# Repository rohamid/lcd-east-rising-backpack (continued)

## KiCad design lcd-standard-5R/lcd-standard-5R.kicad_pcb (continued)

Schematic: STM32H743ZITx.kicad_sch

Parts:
BT1: S8411-45R; CR1220-Batt-conn-S8411-45R; JLCPCB Part # C70381
C6, C7, C9, C11, C13, C14, C15, C16, C17, C18, C19, C20, C21, C22, C23, C29: 100n; C_0402_1005Metric; JLCPCB Part # C307331
C8: 1u; C_0603_1608Metric; JLCPCB Part # C15849
C10, C12: 2u2; C_0603_1608Metric; JLCPCB Part # C23630
C24: 4u7; C_0603_1608Metric; JLCPCB Part # C19666
C25, C26: 16p; C_0402_1005Metric; JLCPCB Part # C77590
C27, C28: 10p; C_0402_1005Metric; JLCPCB Part # C32949
D3: BAT54CW; SOT-23; JLCPCB Part # C37704
D4: B5819WS; D_SOD-123; JLCPCB Part # C8598
J2: SWD; PinHeader_2x07_P1.27mm_Vertical_SMD; JLCPCB Part # C5160763
J11: TAG_CONNECT; Tag-Connect_TC2050-IDC-NL_2x05_P1.27mm_Vertical
R6, R7, R8: 10K; R_0402_1005Metric; JLCPCB Part # C25744
SW1, SW2: SW_Push; SW_SPST_PTS810; JLCPCB Part # C127488
U3: STM32H743ZITx; LQFP-144_20x20mm_P0.5mm; JLCPCB Part # C114408
Y1: 25MHz; Crystal_SMD_2520-4Pin_2.5x2.0mm; JLCPCB Part # C255954
Y2: 32.768KHz; Crystal_SMD_2012-2Pin_2.0x1.2mm; JLCPCB Part # C99009

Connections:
+3V3: C6.1, C7.1, C8.1, C9.1, C11.1, C14.1, C15.1, C16.1, C17.1, C18.1, C19.1, C20.1, C21.1, C22.1, C23.1, C24.1, D3.2, J2.3, J11.7, R6.1, R7.1, SW1.2, U3.17 (VDD), U3.30 (VDD), U3.32 (VREF+), U3.33 (VDDA), U3.39 (VDD), U3.52 (VDD), U3.62 (VDD), U3.72 (VDD), U3.84 (VDD), U3.95 (VDD33_USB), U3.108 (VDD), U3.121 (VDD), U3.131 (VDD), U3.144 (VDD); also elsewhere on the board
/DISPLAY/CTP_INT: U3.80 (PD11); also elsewhere on the board
/DISPLAY/CTP_RST: U3.98 (PC8); also elsewhere on the board
/DISPLAY/CTP_SCL: U3.100 (PA8); also elsewhere on the board
/DISPLAY/CTP_SDA: U3.99 (PC9); also elsewhere on the board
/DISPLAY/CTP_WAKE: U3.88 (PG3); also elsewhere on the board
/DISPLAY/LCD_B0: U3.3 (PE4); also elsewhere on the board
/DISPLAY/LCD_B1: U3.127 (PG12); also elsewhere on the board
/DISPLAY/LCD_B2: U3.122 (PD6); also elsewhere on the board
/DISPLAY/LCD_B3: U3.126 (PG11); also elsewhere on the board
/DISPLAY/LCD_B4: U3.102 (PA10); also elsewhere on the board
/DISPLAY/LCD_B5: U3.37 (PA3); also elsewhere on the board
/DISPLAY/LCD_B6: U3.139 (PB8); also elsewhere on the board
/DISPLAY/LCD_B7: U3.140 (PB9); also elsewhere on the board
/DISPLAY/LCD_BLK: U3.110 (PA15); also elsewhere on the board
/DISPLAY/LCD_CLK: U3.92 (PG7); also elsewhere on the board
/DISPLAY/LCD_DE: U3.22 (PF10); also elsewhere on the board
/DISPLAY/LCD_G0: U3.4 (PE5); also elsewhere on the board
/DISPLAY/LCD_G1: U3.5 (PE6); also elsewhere on the board
/DISPLAY/LCD_G2: U3.42 (PA6); also elsewhere on the board
/DISPLAY/LCD_G3: U3.125 (PG10); also elsewhere on the board
/DISPLAY/LCD_G4: U3.69 (PB10); also elsewhere on the board
/DISPLAY/LCD_G5: U3.70 (PB11); also elsewhere on the board
/DISPLAY/LCD_G6: U3.97 (PC7); also elsewhere on the board
/DISPLAY/LCD_G7: U3.117 (PD3); also elsewhere on the board
/DISPLAY/LCD_HSYNC: U3.96 (PC6); also elsewhere on the board
/DISPLAY/LCD_R0: U3.128 (PG13); also elsewhere on the board
/DISPLAY/LCD_R1: U3.36 (PA2); also elsewhere on the board
/DISPLAY/LCD_R2: U3.35 (PA1); also elsewhere on the board
/DISPLAY/LCD_R3: U3.46 (PB0); also elsewhere on the board
/DISPLAY/LCD_R4: U3.41 (PA5); also elsewhere on the board
/DISPLAY/LCD_R5: U3.26 (PC0); also elsewhere on the board
/DISPLAY/LCD_R6: U3.47 (PB1); also elsewhere on the board
/DISPLAY/LCD_R7: U3.91 (PG6); also elsewhere on the board
/DISPLAY/LCD_VSYNC: U3.40 (PA4); also elsewhere on the board
/DISPLAY/RTP_BUSY: U3.116 (PD2); also elsewhere on the board
/DISPLAY/RTP_CLK: U3.111 (PC10); also elsewhere on the board
/DISPLAY/RTP_CS: U3.119 (PD5); also elsewhere on the board
/DISPLAY/RTP_IRQ: U3.118 (PD4); also elsewhere on the board
/DISPLAY/RTP_MISO: U3.112 (PC11); also elsewhere on the board
/DISPLAY/RTP_MOSI: U3.113 (PC12); also elsewhere on the board
/IO/BTN_0: U3.7 (PC13); also elsewhere on the board
/IO/BTN_1: U3.123 (PD7); also elsewhere on the board
/IO/BUZZER: U3.135 (PB5); also elsewhere on the board
/IO/LED0: U3.1 (PE2); also elsewhere on the board
/IO/SERIAL_RX: U3.129 (PG14); also elsewhere on the board
/IO/SERIAL_TX: U3.124 (PG9); also elsewhere on the board
/MCU/BOOT0: R8.1, SW1.1, U3.138 (BOOT0)
/MCU/NRST: C29.1, J2.12, J11.5, R7.2, SW2.1, U3.25 (NRST)
/MCU/OSC32_IN: C27.1, U3.8 (PC14), Y2.2
/MCU/OSC32_OUT: C28.1, U3.9 (PC15), Y2.1
/MCU/SDRAM_ADD0: U3.10 (PF0); also elsewhere on the board
/MCU/SDRAM_ADD1: U3.11 (PF1); also elsewhere on the board
/MCU/SDRAM_ADD2: U3.12 (PF2); also elsewhere on the board
/MCU/SDRAM_ADD3: U3.13 (PF3); also elsewhere on the board
/MCU/SDRAM_ADD4: U3.14 (PF4); also elsewhere on the board
/MCU/SDRAM_ADD5: U3.15 (PF5); also elsewhere on the board
/MCU/SDRAM_ADD6: U3.50 (PF12); also elsewhere on the board
/MCU/SDRAM_ADD7: U3.53 (PF13); also elsewhere on the board
/MCU/SDRAM_ADD8: U3.54 (PF14); also elsewhere on the board
/MCU/SDRAM_ADD9: U3.55 (PF15); also elsewhere on the board
/MCU/SDRAM_ADD10: U3.56 (PG0); also elsewhere on the board
/MCU/SDRAM_ADD11: U3.57 (PG1); also elsewhere on the board
/MCU/SDRAM_ADD12: U3.87 (PG2); also elsewhere on the board
/MCU/SDRAM_DQ0: U3.85 (PD14); also elsewhere on the board
/MCU/SDRAM_DQ1: U3.86 (PD15); also elsewhere on the board
/MCU/SDRAM_DQ2: U3.114 (PD0); also elsewhere on the board
/MCU/SDRAM_DQ3: U3.115 (PD1); also elsewhere on the board
/MCU/SDRAM_DQ4: U3.58 (PE7); also elsewhere on the board
/MCU/SDRAM_DQ5: U3.59 (PE8); also elsewhere on the board
/MCU/SDRAM_DQ6: U3.60 (PE9); also elsewhere on the board
/MCU/SDRAM_DQ7: U3.63 (PE10); also elsewhere on the board
/MCU/SDRAM_DQ8: U3.64 (PE11); also elsewhere on the board
/MCU/SDRAM_DQ9: U3.65 (PE12); also elsewhere on the board
/MCU/SDRAM_DQ10: U3.66 (PE13); also elsewhere on the board
/MCU/SDRAM_DQ11: U3.67 (PE14); also elsewhere on the board
/MCU/SDRAM_DQ12: U3.68 (PE15); also elsewhere on the board
/MCU/SDRAM_DQ13: U3.77 (PD8); also elsewhere on the board
/MCU/SDRAM_DQ14: U3.78 (PD9); also elsewhere on the board
/MCU/SDRAM_DQ15: U3.79 (PD10); also elsewhere on the board
/MCU/SD_D0: U3.75 (PB14); also elsewhere on the board
/MCU/SD_D1: U3.76 (PB15); also elsewhere on the board
/MCU/SD_D2: U3.133 (PB3); also elsewhere on the board
/MCU/SD_D3: U3.134 (PB4); also elsewhere on the board
/MCU/ST_LINK_RX: J2.13, U3.137 (PB7)
/MCU/ST_LINK_TX: J2.14, U3.101 (PA9)
/MCU/SWCLK: J2.6, J11.6, U3.109 (PA14)
/MCU/SWDIO: J2.4, J11.2, U3.105 (PA13)
/MCU/XIN: C25.1, U3.23 (PH0), Y1.3
/MCU/XOUT: C26.1, U3.24 (PH1), Y1.1
/MEMORY_EEPROM/EE_SCL: U3.81 (PD12); also elsewhere on the board
/MEMORY_EEPROM/EE_SDA: U3.82 (PD13); also elsewhere on the board
/MEMORY_FLASH/NOR_CLK: U3.48 (PB2); also elsewhere on the board
/MEMORY_FLASH/NOR_DI(IO0): U3.21 (PF9); also elsewhere on the board
/MEMORY_FLASH/NOR_DO(IO1): U3.20 (PF8); also elsewhere on the board
/MEMORY_FLASH/NOR_IO2: U3.19 (PF7); also elsewhere on the board
/MEMORY_FLASH/NOR_IO3: U3.18 (PF6); also elsewhere on the board
/MEMORY_FLASH/~NOR_CS: U3.136 (PB6); also elsewhere on the board
/MEMORY_FMC/SDRAM_BA0: U3.89 (PG4); also elsewhere on the board
/MEMORY_FMC/SDRAM_BA1: U3.90 (PG5); also elsewhere on the board
/MEMORY_FMC/SDRAM_CKE: U3.45 (PC5); also elsewhere on the board
/MEMORY_FMC/SDRAM_CLK: U3.93 (PG8); also elsewhere on the board
/MEMORY_FMC/SDRAM_LDQM: U3.141 (PE0); also elsewhere on the board
/MEMORY_FMC/SDRAM_UDQM: U3.142 (PE1); also elsewhere on the board
/MEMORY_FMC/~SDRAM_CAS: U3.132 (PG15); also elsewhere on the board
/MEMORY_FMC/~SDRAM_CS: U3.44 (PC4); also elsewhere on the board
/MEMORY_FMC/~SDRAM_RAS: U3.49 (PF11); also elsewhere on the board
/MEMORY_FMC/~SDRAM_WE: U3.43 (PA7); also elsewhere on the board
/MEMORY_SD_CARD/SD_CLK: U3.27 (PC1); also elsewhere on the board
/MEMORY_SD_CARD/SD_CMD: U3.34 (PA0); also elsewhere on the board
/MEMORY_SD_CARD/SD_DET: U3.28 (PC2_C); also elsewhere on the board
/OUTPUT_SPEAKER/I2S2_CLK: U3.74 (PB13); also elsewhere on the board
/OUTPUT_SPEAKER/I2S2_SDO: U3.29 (PC3_C); also elsewhere on the board
/OUTPUT_SPEAKER/I2S2_WS: U3.73 (PB12); also elsewhere on the board
/OUTPUT_SPEAKER/~SD_MODE: U3.2 (PE3); also elsewhere on the board
/USB_POWER/D+: U3.104 (PA12); also elsewhere on the board
/USB_POWER/D-: U3.103 (PA11); also elsewhere on the board
GND: BT1.N, C6.2, C7.2, C8.2, C9.2, C10.2, C11.2, C12.2, C13.2, C14.2, C15.2, C16.2, C17.2, C18.2, C19.2, C20.2, C21.2, C22.2, C23.2, C24.2, C25.2, C26.2, C27.2, C28.2, C29.2, J2.2, J2.5, J2.7, J11.3, J11.4, R8.2, SW2.2, U3.16 (VSS), U3.31 (VSSA), U3.38 (VSS), U3.51 (VSS), U3.61 (VSS), U3.83 (VSS), U3.94 (VSS), U3.107 (VSS), U3.120 (VSS), U3.130 (VSS), Y1.2, Y1.4; also elsewhere on the board
unnamed: C10.1, C12.1, U3.71 (VCAP), U3.106 (VCAP)
unnamed: D4.2 (A), J2.1
unnamed: R6.2, U3.143 (PDR_ON)
VB: BT1.P, D3.1
VBAT: C13.1, D3.3, U3.6 (VBAT)
VDD: D4.1 (K); also elsewhere on the board

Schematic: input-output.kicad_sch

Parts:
BZ1: MLT-9650; active-MLT-9650; JLCPCB Part # C255327
C58, C59: 100n; C_0402_1005Metric; JLCPCB Part # C307331
D10, D11: RED; LED_0805_2012Metric; JLCPCB Part # C84256
D12, D13: BAT54S; SOT-23; JLCPCB Part # C47546
J8: Serial; S4BXHSM4TBLFSN; JLCPCB Part # C146120
J9: AUX_IO; Conn_FPC_10P_1mm_G-SWITCH_GT-F1008SR20-10SMT01; JLCPCB Part # C22387155
JP6: JMP; SolderJumper-2_P1.3mm_Open_RoundedPad1.0x1.5mm
Q2, Q3, Q4: MMBT3904; SOT-23; JLCPCB Part # C7420353
R30, R33, R36: 1K; R_0402_1005Metric; JLCPCB Part # C11702
R31, R34, R37, R41, R42: 10K; R_0402_1005Metric; JLCPCB Part # C25744
R32, R35: 2K; R_0402_1005Metric; JLCPCB Part # C4109
SW3: BOOT0; SW_SPST_PTS810; JLCPCB Part # C127488
SW4: RST; SW_SPST_PTS810; JLCPCB Part # C127488

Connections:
+3V3: D12.2 (K), D13.2 (K), R32.2, R35.2, R41.1, R42.1; also elsewhere on the board
/IO/BTN_0: C58.1, R41.2, SW3.1; also elsewhere on the board
/IO/BTN_1: C59.1, R42.2, SW4.1; also elsewhere on the board
/IO/BUZZER: R36.1; also elsewhere on the board
/IO/IO_0: J9.9
/IO/IO_1: J9.8
/IO/IO_2: J9.7
/IO/IO_3: J9.6
/IO/IO_4: J9.5
/IO/IO_5: J9.4
/IO/IO_6: J9.3
/IO/IO_7: J9.2
/IO/LED0: R30.1; also elsewhere on the board
/IO/SERIAL_RX: D13.3 (COM), J8.3; also elsewhere on the board
/IO/SERIAL_TX: D12.3 (COM), J8.2; also elsewhere on the board
/OUTPUT_SPEAKER/~SD_MODE: JP6.2 (B); also elsewhere on the board
GND: C58.2, C59.2, D12.1 (A), D13.1 (A), J8.4, J8.MP (MountPin), J9.1, J9.10, J9.MP (MountPin), Q2.2 (E), Q3.2 (E), Q4.2 (E), R31.2, R34.2, R37.2, SW3.2, SW4.2; also elsewhere on the board
unnamed: BZ1.2 (-), Q4.3 (C)
unnamed: D10.2 (A), R32.1
unnamed: D10.1 (K), Q2.3 (C)
unnamed: D11.2 (A), R35.1
unnamed: D11.1 (K), Q3.3 (C)
unnamed: JP6.1 (A), R33.1
unnamed: Q2.1 (B), R30.2, R31.1
unnamed: Q3.1 (B), R33.2, R34.1
unnamed: Q4.1 (B), R36.2, R37.1
VDD: BZ1.1 (+); also elsewhere on the board
VEXT: J8.1; also elsewhere on the board

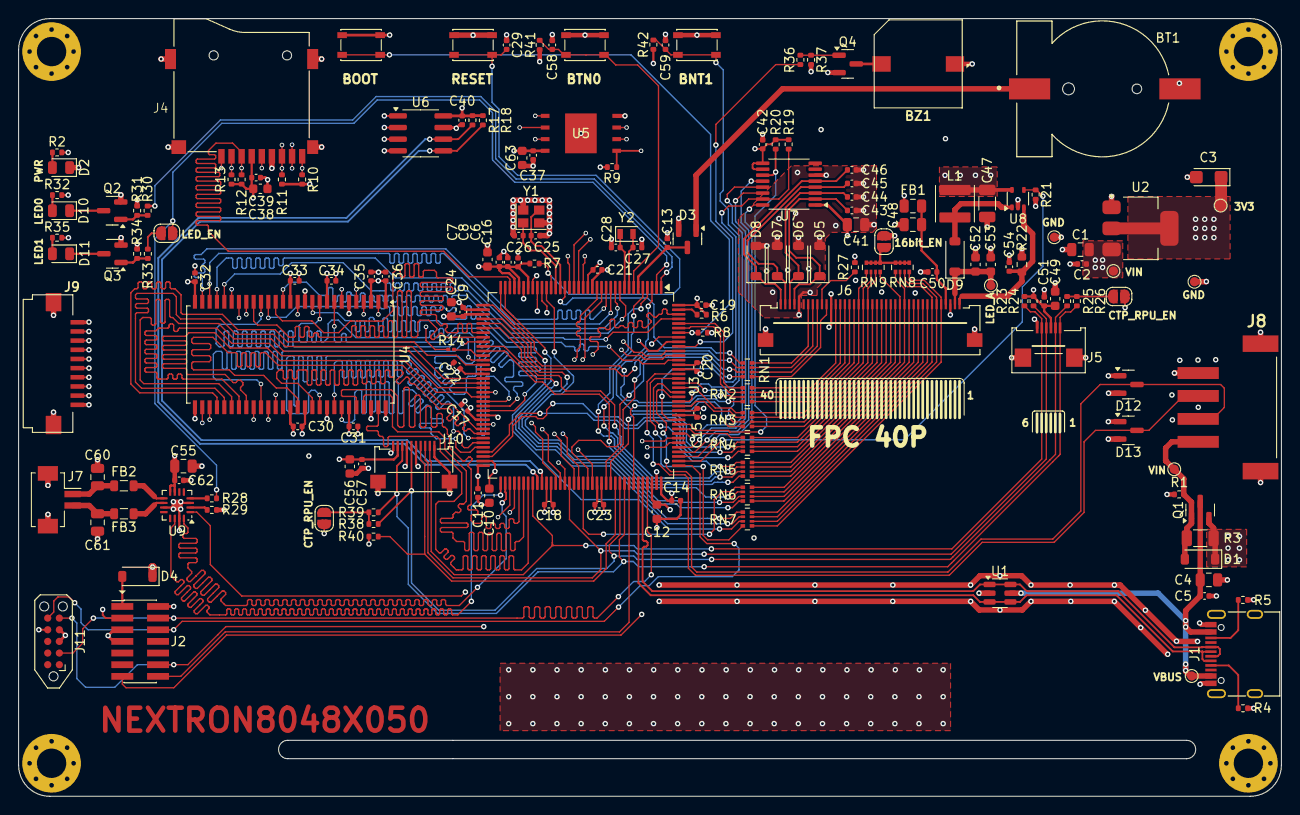
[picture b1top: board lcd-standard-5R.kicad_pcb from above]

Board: 6 copper layers, 137.7 x 84.8 mm, 175 parts (0 on the bottom side), 185 nets.

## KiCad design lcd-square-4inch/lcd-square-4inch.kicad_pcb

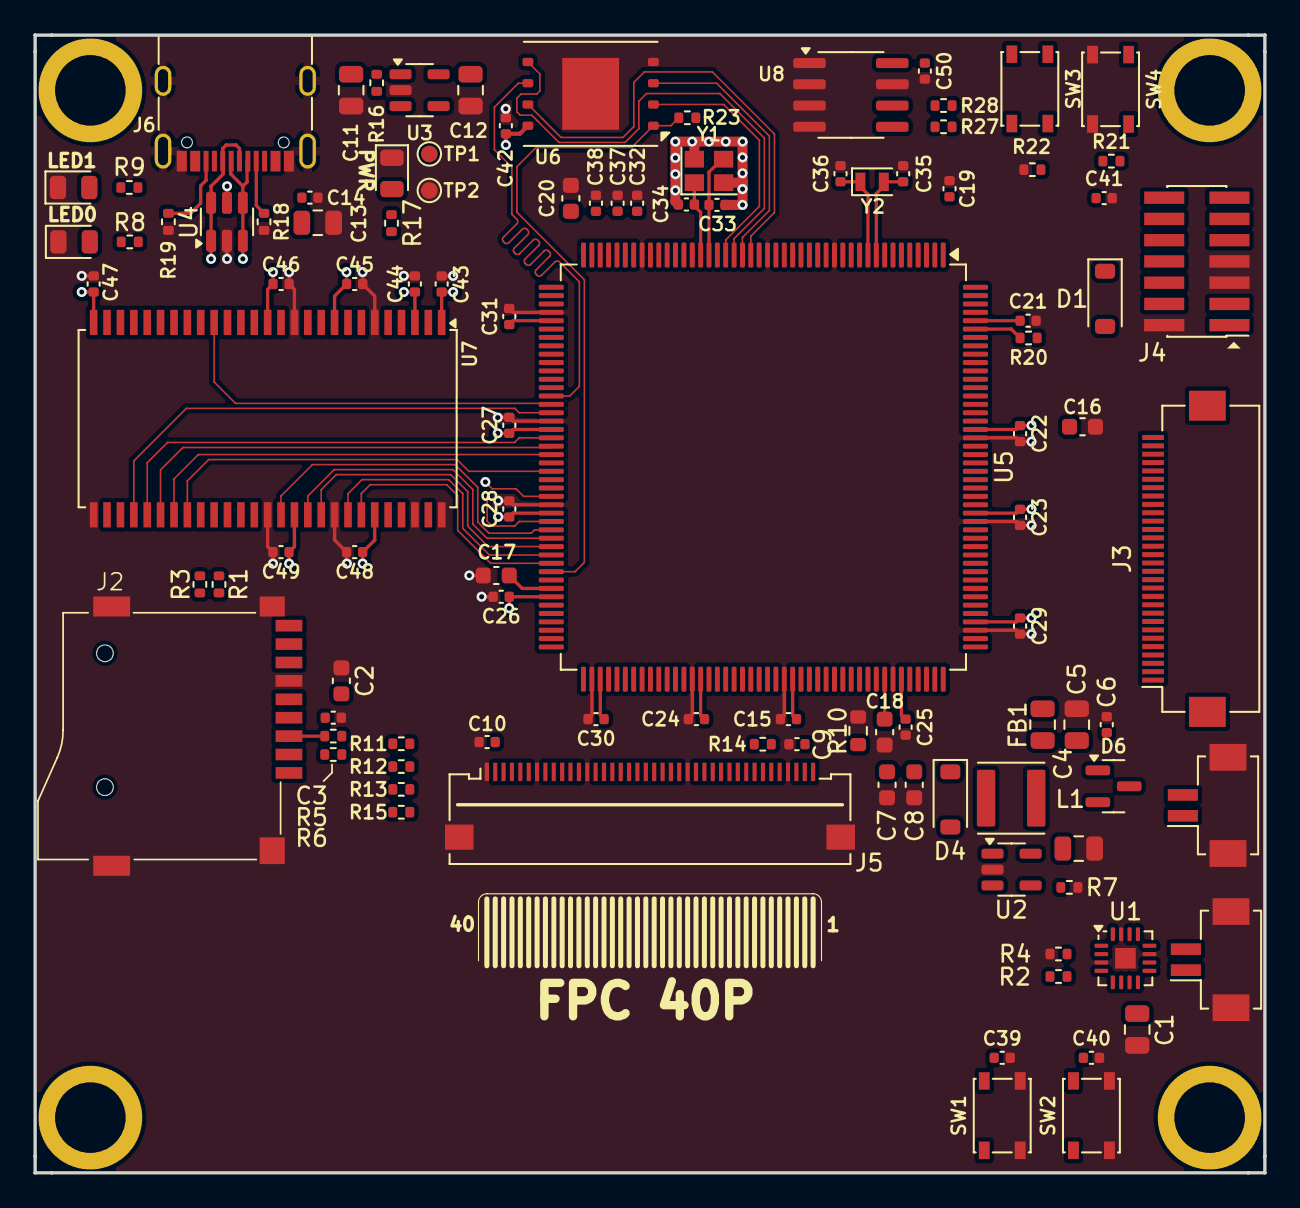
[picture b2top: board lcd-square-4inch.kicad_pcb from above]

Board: 4 copper layers, 73.5 x 68.0 mm, 110 parts (0 on the bottom side), 89 nets.

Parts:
C1, C4, C5: 10u; C_0805_2012Metric
C2, C7, C8, C16: 1u; C_0603_1608Metric
C3, C6, C9, C10, C14, C15, C19, C21, C22, C23, C24, C25, C26, C27, C28, C29, C30, C31, C32, C37, C38, C39, C40, C41, C42, C43, C44, C45, C46, C47, C48, C49, C50: 100n; C_0402_1005Metric
C11: 1uF/0805; C_0805_2012Metric
C12: 2.2u; C_0805_2012Metric
C13: 4u7; C_0805_2012Metric
C17, C18: 2u2; C_0603_1608Metric
C20: 4u7; C_0603_1608Metric
C33, C34: 16p; C_0402_1005Metric
C35, C36: 10p; C_0402_1005Metric
D1: NSR0320MW2T1G; D_SOD-123
D2, D3: RED; LED_0805_2012Metric
D4: MBR0540; D_SOD-123
D5: GREEN; LED_0805_2012Metric
D6: BAT54CW; SOT-23
FB1: 600R/100MHz; C_0805_2012Metric
H1, H2, H3, H4: MountingHole; SMTSO30xx
J1, J1#2: Conn_01x02_MountingPin; Hirose_DF13C_CL535-0402-2-51_1x02-1MP_P1.25mm_Vertical
J2: Micro_SD_Card_Det1; SD-TF-115
J3: Conn_01x30_MountingPin; Hirose_FH12-30S-0.5SH_1x30-1MP_P0.50mm_Horizontal
J4: SWD; PinHeader_2x07_P1.27mm_Vertical_SMD
J5: Conn_01x40_MountingPin; Omron_XF2M-4015-1A_1x40-1MP_P0.5mm_Horizontal
J6: USB_C_Receptacle_USB2.0_16P; USB_C_Receptacle_G-Switch_GT-USB-7010ASV
L1: 4.7u; L_Abracon_ASPI-4030S
R1, R3, R5, R6, R7, R11, R14, R15, R16, R20, R21, R22, R23: 10K; R_0402_1005Metric
R2: 1M; R_0402_1005Metric
R4: 100K; R_0402_1005Metric
R8, R9: 2K; R_0402_1005Metric
R10: 6.8R; R_0603_1608Metric
R12, R13, R17, R27, R28: 2K2; R_0402_1005Metric
R18, R19: 5K1; R_0402_1005Metric
SW1, SW2, SW3, SW4: SW_Push; SW_SPST_PTS810
TP1, TP2: TestPoint; TestPoint_Pad_D1.0mm
U1: MAX98357A; TQFN-16-1EP_3x3mm_P0.5mm_EP1.23x1.23mm
U2: TPS61169; SOT-23-5
U3: TLV75733PDBV; SOT-23-5
U4: USBLC6-2SC6; SOT-23-6
U5: STM32H743IITx; LQFP-176_24x24mm_P0.5mm
U6: MT25Q; WSON-8-1EP_8x6mm_P1.27mm_EP3.4x4.3mm
U7: MT48LC16M16A2P; TSOP-II-54_22.2x10.16mm_P0.8mm
U8: CAT24C256; SOIC-8_3.9x4.9mm_P1.27mm
Y1: 25MHz; Crystal_SMD_2520-4Pin_2.5x2.0mm
Y2: 32.768KHz; Crystal_SMD_2012-2Pin_2.0x1.2mm

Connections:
+3V3: C2.1, C3.1, C10.1, C12.1, C15.1, C16.1, C20.1, C21.1, C22.1, C23.1, C24.1, C25.1, C26.1, C27.1, C28.1, C29.1, C30.1, C31.1, C32.1, C37.1, C38.1, C42.1, C43.1, C44.1, C45.1, C46.1, C47.1, C48.1, C49.1, C50.1, D6.2, FB1.1, J2.4 (VDD), J4.3, J5.2, R1.1, R3.1, R5.1, R6.1, R11.1, R12.1, R13.1, R14.1, R15.1, R17.1, R20.1, R21.1, R23.1, R27.1, R28.1, SW3.2, TP1.1, U3.5 (OUT), U5.15 (VDD), U5.23 (VDD), U5.36 (VDD), U5.38 (VREF+), U5.39 (VDDA), U5.49 (VDD), U5.62 (VDD), U5.72 (VDD), U5.82 (VDD), U5.91 (VDD), U5.103 (VDD), U5.114 (VDD33_USB), U5.127 (VDD), U5.136 (VDD), U5.149 (VDD), U5.159 (VDD), U5.172 (VDD), U6.8 (VCC), U7.1 (VDD), U7.3 (VDDQ), U7.9 (VDDQ), U7.14 (VDD), U7.27 (VDD), U7.43 (VDDQ), U7.49 (VDDQ), U8.8 (VCC)
/CMD: J2.3 (CMD), R5.2
/DAT0: J2.7 (DAT0), R3.2
/DAT3: J2.2 (DAT3/CD), R6.2
/EEPROM/EE_SCL: R28.2, U8.6 (SCL)
/EEPROM/EE_SDA: R27.2, U8.5 (SDA)
/LCD_BLK: R7.1, U2.4 (EN)
/LCD_RST: J5.35, R14.2
/LCD_TP_INT: J5.6, R15.2
/LCD_TP_RST: J5.3, R11.2
/LCD_TP_SCL: J5.4, R12.2
/LCD_TP_SDA: J5.5, R13.2
/LED_A: C7.1, C8.1, D4.1 (K), J5.40
/LED_K: C9.1, J5.38, J5.39, R10.1, U2.3 (FB)
/MCU/BOOT0: R22.1, SW3.1, U5.166 (BOOT0)
/MCU/BTN0: C40.1, SW2.1, U5.99 (PD11)
/MCU/BTN1: C39.1, SW1.1, U5.84 (PH7)
/MCU/NRST: C41.1, R21.2, SW4.1, U5.31 (NRST)
/MCU/OSC32_IN: C35.1, U5.9 (PC14), Y2.2
/MCU/OSC32_OUT: C36.1, U5.10 (PC15), Y2.1
/MCU/QUADSPI_BK1_IO0: U5.26 (PF8), U6.5 (DI(IO0))
/MCU/QUADSPI_BK1_IO1: U5.27 (PF9), U6.2 (DO(IO1))
/MCU/QUADSPI_BK1_IO2: U5.25 (PF7), U6.3 (IO2)
/MCU/QUADSPI_BK1_IO3: U5.24 (PF6), U6.7 (IO3)
/MCU/QUADSPI_BK1_NCS: R23.2, U5.79 (PB10), U6.1 (~CS)
/MCU/QUADSPI_CLK: U5.58 (PB2), U6.6 (CLK)
/MCU/SDRAM_ADD0: U5.16 (PF0), U7.23 (A0)
/MCU/SDRAM_ADD1: U5.17 (PF1), U7.24 (A1)
/MCU/SDRAM_ADD2: U5.18 (PF2), U7.25 (A2)
/MCU/SDRAM_ADD3: U5.19 (PF3), U7.26 (A3)
/MCU/SDRAM_ADD4: U5.20 (PF4), U7.29 (A4)
/MCU/SDRAM_ADD5: U5.21 (PF5), U7.30 (A5)
/MCU/SDRAM_ADD6: U5.60 (PF12), U7.31 (A6)
/MCU/SDRAM_ADD7: U5.63 (PF13), U7.32 (A7)
/MCU/SDRAM_ADD8: U5.64 (PF14), U7.33 (A8)
/MCU/SDRAM_ADD9: U5.65 (PF15), U7.34 (A9)
/MCU/SDRAM_ADD10: U5.66 (PG0), U7.22 (A10)
/MCU/SDRAM_ADD11: U5.67 (PG1), U7.35 (A11)
/MCU/SDRAM_ADD12: U5.106 (PG2), U7.36 (A12)
/MCU/SDRAM_DQ0: U5.104 (PD14), U7.2 (DQ0)
/MCU/SDRAM_DQ1: U5.105 (PD15), U7.4 (DQ1)
/MCU/SDRAM_DQ2: U5.142 (PD0), U7.5 (DQ2)
/MCU/SDRAM_DQ3: U5.143 (PD1), U7.7 (DQ3)
/MCU/SDRAM_DQ4: U5.68 (PE7), U7.8 (DQ4)
/MCU/SDRAM_DQ5: U5.69 (PE8), U7.10 (DQ5)
/MCU/SDRAM_DQ6: U5.70 (PE9), U7.11 (DQ6)
/MCU/SDRAM_DQ7: U5.73 (PE10), U7.13 (DQ7)
/MCU/SDRAM_DQ8: U5.74 (PE11), U7.42 (DQ8)
/MCU/SDRAM_DQ9: U5.75 (PE12), U7.44 (DQ9)
/MCU/SDRAM_DQ10: U5.76 (PE13), U7.45 (DQ10)
/MCU/SDRAM_DQ11: U5.77 (PE14), U7.47 (DQ11)
/MCU/SDRAM_DQ12: U5.78 (PE15), U7.48 (DQ12)
/MCU/SDRAM_DQ13: U5.96 (PD8), U7.50 (DQ13)
/MCU/SDRAM_DQ14: U5.97 (PD9), U7.51 (DQ14)
/MCU/SDRAM_DQ15: U5.98 (PD10), U7.53 (DQ15)
/MCU/XIN: C33.1, U5.29 (PH0), Y1.3
/MCU/XOUT: C34.1, U5.30 (PH1), Y1.1
/SDRAM/SDRAM_BA0: U5.108 (PG4), U7.20 (BA0)
/SDRAM/SDRAM_BA1: U5.109 (PG5), U7.21 (BA1)
/SDRAM/SDRAM_CKE: U5.55 (PC5), U7.37 (CKE)
/SDRAM/SDRAM_CLK: U5.112 (PG8), U7.38 (CLK)
/SDRAM/SDRAM_LDQM: U5.169 (PE0), U7.15 (DQML)
/SDRAM/SDRAM_UDQM: U5.170 (PE1), U7.39 (DQMH)
/SDRAM/~SDRAM_CAS: U5.160 (PG15), U7.17 (~CAS)
/SDRAM/~SDRAM_CS: U5.54 (PC4), U7.19 (~CS)
/SDRAM/~SDRAM_RAS: U5.59 (PF11), U7.18 (~RAS)
/SDRAM/~SDRAM_WE: U5.53 (PA7), U7.16 (~WE)
/SD_DET: J2.9 (DET), R1.2
/SW: D4.2 (A), L1.2, U2.1 (SW)
/USB_POWER/D+: J6.A6 (D+), J6.B6 (D+), U4.1 (I/O1), U4.6 (I/O1)
/USB_POWER/D-: J6.A7 (D-), J6.B7 (D-), U4.3 (I/O2), U4.4 (I/O2)
GND: C1.2, C2.2, C3.2, C4.2, C5.2, C6.2, C7.2, C8.2, C9.2, C10.2, C11.2, C12.2, C13.2, C14.2, C15.2, C16.2, C17.2, C18.2, C19.2, C20.2, C21.2, C22.2, C23.2, C24.2, C25.2, C26.2, C27.2, C28.2, C29.2, C30.2, C31.2, C32.2, C33.2, C34.2, C35.2, C36.2, C37.2, C38.2, C39.2, C40.2, C41.2, C42.2, C43.2, C44.2, C45.2, C46.2, C47.2, C48.2, C49.2, C50.2, D2.1 (K), D3.1 (K), D5.1 (K), J1.MP (MountPin), J1#2.MP (MountPin), J2.6 (VSS), J2.10 (SHIELD), J4.2, J4.5, J4.7, J5.1, J5.7, J5.13, J5.25, J5.37, J5.MP (MountPin), J6.A1 (GND), J6.A12 (GND), J6.B1 (GND), J6.B12 (GND), J6.S1 (SHIELD), R4.2, R7.2, R10.2, R18.1, R19.1, R22.2, SW1.2, SW2.2, SW4.2, TP2.1, U1.3 (GND), U1.11 (GND), U1.15 (GND), U1.17 (PAD), U2.2 (GND), U3.2 (GND), U4.2 (GND), U5.14 (VSS), U5.22 (VSS), U5.37 (VSSA), U5.48 (VSS), U5.61 (VSS), U5.71 (VSS), U5.90 (VSS), U5.102 (VSS), U5.113 (VSS), U5.126 (VSS), U5.135 (VSS), U5.148 (VSS), U5.158 (VSS), U6.4 (GND), U6.9 (EP), U7.6 (VSSQ), U7.12 (VSSQ), U7.28 (VSS), U7.41 (VSS), U7.46 (VSSQ), U7.52 (VSSQ), U7.54 (VSS), U8.1 (A0), U8.2 (A1), U8.3 (A2), U8.4 (GND), U8.7 (WP), Y1.2, Y1.4
unnamed: C17.1, C18.1, U5.81 (VCAP), U5.125 (VCAP)
unnamed: D1.2 (A), J4.1
unnamed: D2.2 (A), R8.2
unnamed: D3.2 (A), R9.2
unnamed: D5.2 (A), R17.2
unnamed: J1.1, J1#2.1, U1.9 (OUTP)
unnamed: J1.2, J1#2.2, U1.10 (OUTN)
unnamed: J6.A5 (CC1), R18.2
unnamed: J6.B5 (CC2), R19.2
unnamed: R4.1, U1.2 (GAIN_SLOT)
unnamed: R2.2, U1.4 (~SD_MODE)
unnamed: R16.2, U3.3 (EN)
unnamed: R20.2, U5.171 (PDR_ON)
VBAT: C19.1, D6.3, U5.6 (VBAT)
VBUS: C1.1, C4.1, C13.1, C14.1, D1.1 (K), J6.A4 (VBUS), J6.A9 (VBUS), J6.B4 (VBUS), J6.B9 (VBUS), L1.1, U1.7 (VDD), U1.8 (VDD), U2.5 (VIN), U4.5 (VBUS)
VDD: C11.1, R16.1, U3.1 (IN)
VDD_LCD: C5.1, C6.1, FB1.2, J5.36

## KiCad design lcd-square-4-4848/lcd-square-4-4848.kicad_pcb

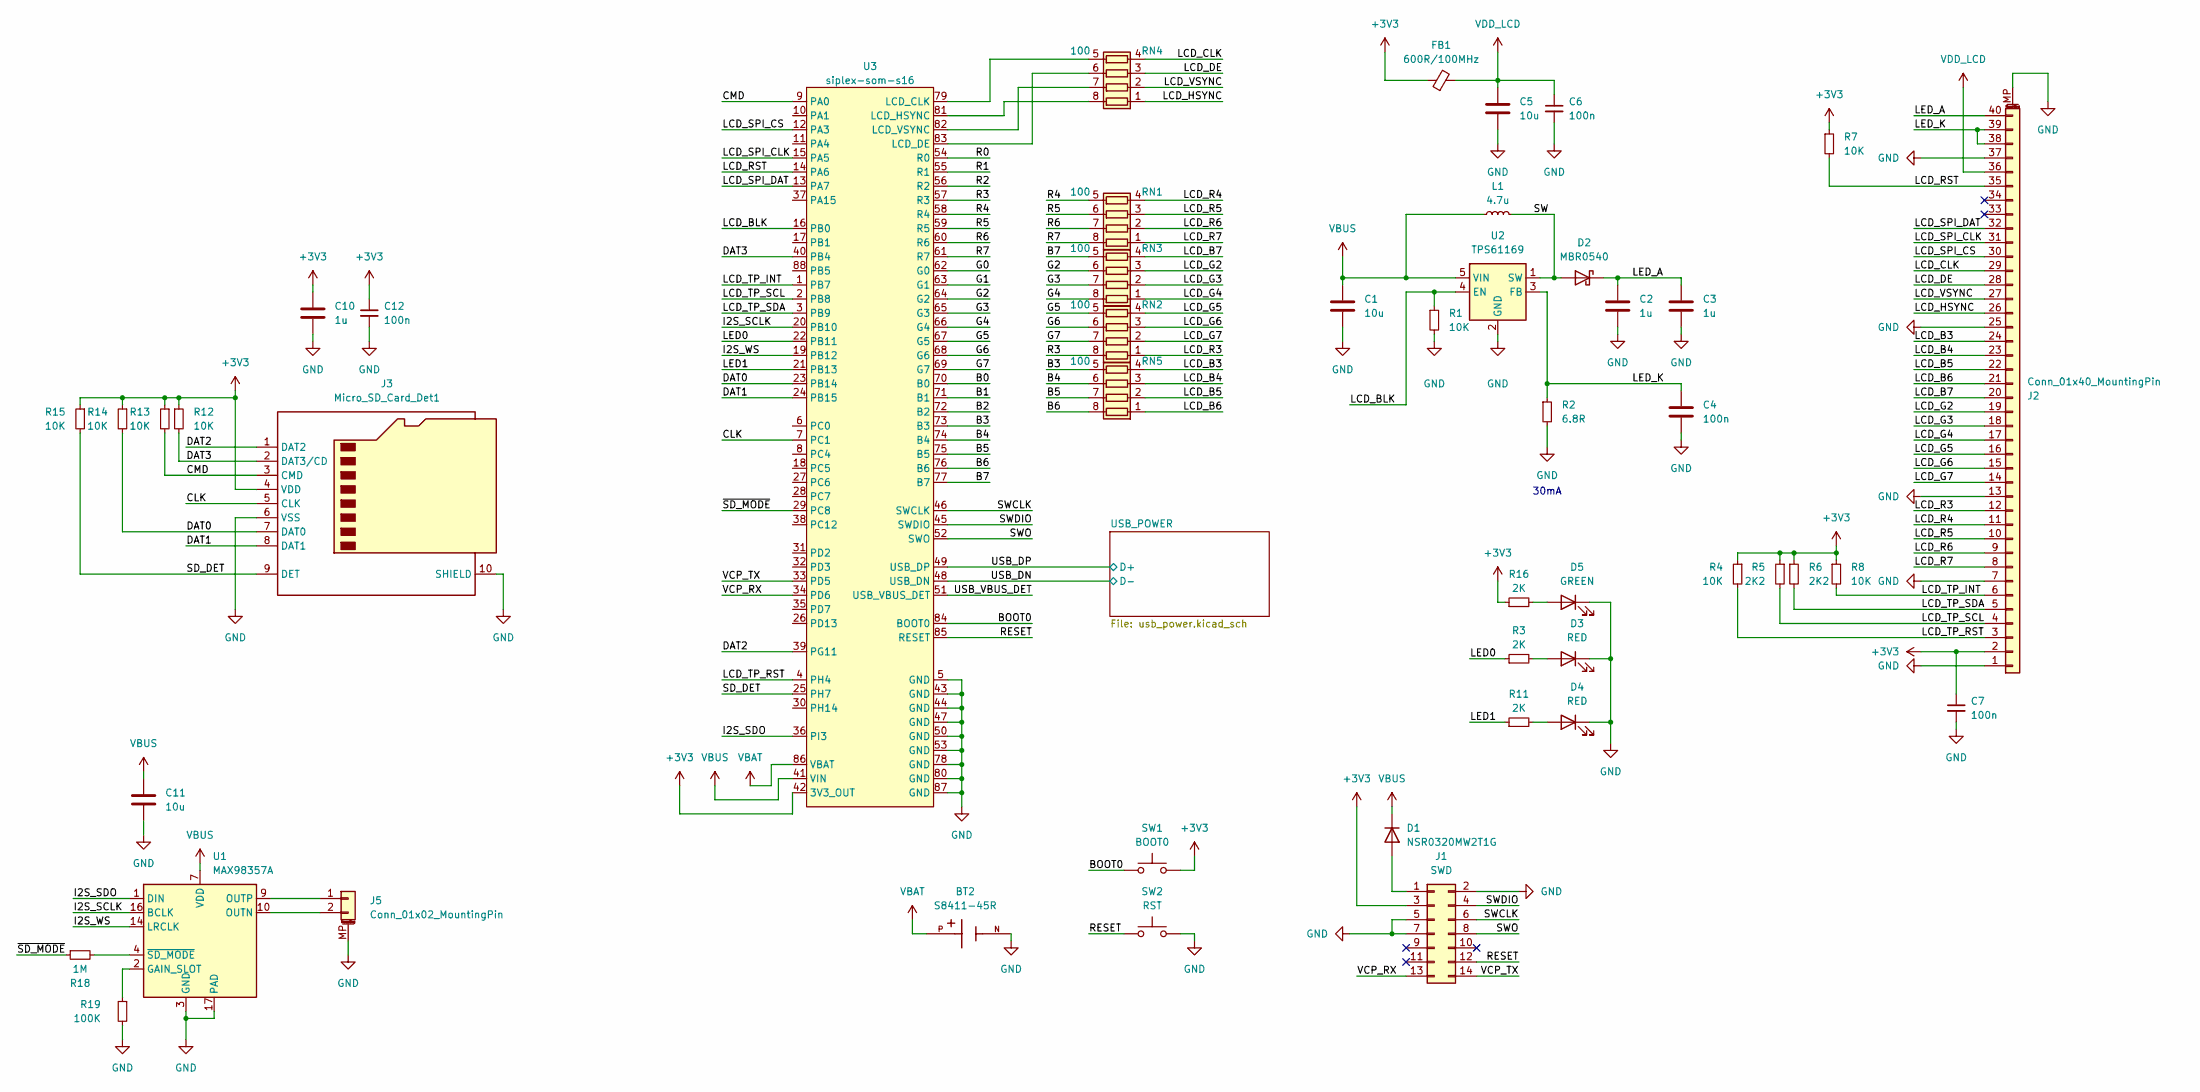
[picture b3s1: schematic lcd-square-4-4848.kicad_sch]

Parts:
BT2: S8411-45R; CR1220-Batt-conn-S8411-45R; JLCPCB Part # C70381
C1, C5, C11: 10u; C_0805_2012Metric; JLCPCB Part # C15850
C2, C3, C10: 1u; C_0603_1608Metric; JLCPCB Part # C15849
C4, C6, C7, C12: 100n; C_0402_1005Metric; JLCPCB Part # C307331
D1: NSR0320MW2T1G; D_SOD-123; JLCPCB Part # C48192
D2: MBR0540; D_SOD-123; JLCPCB Part # C7420330
D3, D4: RED; LED_0805_2012Metric; JLCPCB Part # C84256
D5: GREEN; LED_0805_2012Metric; JLCPCB Part # C2297
FB1: 600R/100MHz; C_0805_2012Metric; JLCPCB Part # C1017
J1: SWD; PinHeader_2x07_P1.27mm_Vertical_SMD; JLCPCB Part # C5160763C5160763
J2: Conn_01x40_MountingPin; Omron_XF2M-4015-1A_1x40-1MP_P0.5mm_Horizontal; JLCPCB Part # C225713
J3: Micro_SD_Card_Det1; SD-TF-115; JLCPCB Part # C266621
J5: Conn_01x02_MountingPin; Hirose_DF13C_CL535-0402-2-51_1x02-1MP_P1.25mm_Vertical; JLCPCB Part # C7419891
L1: 4.7u; L_Abracon_ASPI-4030S; JLCPCB Part # C57269
R1, R4, R7, R8, R12, R13, R14, R15: 10K; R_0402_1005Metric; JLCPCB Part # C25744
R2: 6.8R; R_0603_1608Metric; JLCPCB Part # C228038
R3, R11, R16: 2K; R_0402_1005Metric; JLCPCB Part # C4109
R5, R6: 2K2; R_0402_1005Metric; JLCPCB Part # C25879
R18: 1M; R_0402_1005Metric; JLCPCB Part # C26083
R19: 100K; R_0402_1005Metric; JLCPCB Part # C25741
RN1, RN2, RN3, RN4, RN5: 100; R_Array_Convex_4x0402; JLCPCB Part # C48442
SW1: BOOT0; SW_SPST_PTS810; JLCPCB Part # C127488
SW2: RST; SW_SPST_PTS810; JLCPCB Part # C127488
U1: MAX98357A; TQFN-16-1EP_3x3mm_P0.5mm_EP1.23x1.23mm; JLCPCB Part # C910544
U2: TPS61169; SOT-23-5; JLCPCB Part # C71045
U3: siplex-som-s16

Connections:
+3V3: C7.1, C10.1, C12.1, FB1.1, J1.3, J2.2, J3.4 (VDD), R4.1, R5.1, R6.1, R7.1, R8.1, R12.1, R13.1, R14.1, R15.1, R16.1, SW1.2, U3.42 (3V3_OUT)
/B0: U3.70 (B0)
/B1: U3.71 (B1)
/B2: U3.72 (B2)
/B3: RN5.5 (R4.2), U3.73 (B3)
/B4: RN5.6 (R3.2), U3.74 (B4)
/B5: RN5.7 (R2.2), U3.75 (B5)
/B6: RN5.8 (R1.2), U3.76 (B6)
/B7: RN3.5 (R4.2), U3.77 (B7)
/BOOT0: SW1.1, U3.84 (BOOT0)
/CLK: J3.5 (CLK), U3.7 (PC1)
/CMD: J3.3 (CMD), R13.2, U3.9 (PA0)
/DAT0: J3.7 (DAT0), R14.2, U3.23 (PB14)
/DAT1: J3.8 (DAT1), U3.24 (PB15)
/DAT2: J3.1 (DAT2), U3.39 (PG11)
/DAT3: J3.2 (DAT3/CD), R12.2, U3.40 (PB4)
/G0: U3.62 (G0)
/G1: U3.63 (G1)
/G2: RN3.6 (R3.2), U3.64 (G2)
/G3: RN3.7 (R2.2), U3.65 (G3)
/G4: RN3.8 (R1.2), U3.66 (G4)
/G5: RN2.5 (R4.2), U3.67 (G5)
/G6: RN2.6 (R3.2), U3.68 (G6)
/G7: RN2.7 (R2.2), U3.69 (G7)
/I2S_SCLK: U1.16 (BCLK), U3.20 (PB10)
/I2S_SDO: U1.1 (DIN), U3.36 (PI3)
/I2S_WS: U1.14 (LRCLK), U3.19 (PB12)
/LCD_B3: J2.24, RN5.4 (R4.1)
/LCD_B4: J2.23, RN5.3 (R3.1)
/LCD_B5: J2.22, RN5.2 (R2.1)
/LCD_B6: J2.21, RN5.1 (R1.1)
/LCD_B7: J2.20, RN3.4 (R4.1)
/LCD_BLK: R1.1, U2.4 (EN), U3.16 (PB0)
/LCD_CLK: J2.29, RN4.4 (R4.1)
/LCD_DE: J2.28, RN4.3 (R3.1)
/LCD_G2: J2.19, RN3.3 (R3.1)
/LCD_G3: J2.18, RN3.2 (R2.1)
/LCD_G4: J2.17, RN3.1 (R1.1)
/LCD_G5: J2.16, RN2.4 (R4.1)
/LCD_G6: J2.15, RN2.3 (R3.1)
/LCD_G7: J2.14, RN2.2 (R2.1)
/LCD_HSYNC: J2.26, RN4.1 (R1.1)
/LCD_R3: J2.12, RN2.1 (R1.1)
/LCD_R4: J2.11, RN1.4 (R4.1)
/LCD_R5: J2.10, RN1.3 (R3.1)
/LCD_R6: J2.9, RN1.2 (R2.1)
/LCD_R7: J2.8, RN1.1 (R1.1)
/LCD_RST: J2.35, R7.2, U3.14 (PA6)
/LCD_SPI_CLK: J2.31, U3.15 (PA5)
/LCD_SPI_CS: J2.30, U3.12 (PA3)
/LCD_SPI_DAT: J2.32, U3.13 (PA7)
/LCD_TP_INT: J2.6, R8.2, U3.1 (PB7)
/LCD_TP_RST: J2.3, R4.2, U3.4 (PH4)
/LCD_TP_SCL: J2.4, R5.2, U3.2 (PB8)
/LCD_TP_SDA: J2.5, R6.2, U3.3 (PB9)
/LCD_VSYNC: J2.27, RN4.2 (R2.1)
/LED0: R3.1, U3.22 (PB11)
/LED1: R11.1, U3.21 (PB13)
/LED_A: C2.1, C3.1, D2.1 (K), J2.40
/LED_K: C4.1, J2.38, J2.39, R2.1, U2.3 (FB)
/R0: U3.54 (R0)
/R1: U3.55 (R1)
/R2: U3.56 (R2)
/R3: RN2.8 (R1.2), U3.57 (R3)
/R4: RN1.5 (R4.2), U3.58 (R4)
/R5: RN1.6 (R3.2), U3.59 (R5)
/R6: RN1.7 (R2.2), U3.60 (R6)
/R7: RN1.8 (R1.2), U3.61 (R7)
/RESET: J1.12, SW2.1, U3.85 (RESET)
/SD_DET: J3.9 (DET), R15.2, U3.25 (PH7)
/SW: D2.2 (A), L1.2, U2.1 (SW)
/SWCLK: J1.6, U3.46 (SWCLK)
/SWDIO: J1.4, U3.45 (SWDIO)
/SWO: J1.8, U3.52 (SWO)
/USB_DN: U3.48 (USB_DN); also elsewhere on the board
/USB_DP: U3.49 (USB_DP); also elsewhere on the board
/USB_VBUS_DET: U3.51 (USB_VBUS_DET)
/VCP_RX: J1.13, U3.34 (PD6)
/VCP_TX: J1.14, U3.33 (PD5)
/~SD_MODE: R18.1, U3.29 (PC8)
GND: BT2.N, C1.2, C2.2, C3.2, C4.2, C5.2, C6.2, C7.2, C10.2, C11.2, C12.2, D3.1 (K), D4.1 (K), D5.1 (K), J1.2, J1.5, J1.7, J2.1, J2.7, J2.13, J2.25, J2.37, J2.MP (MountPin), J3.6 (VSS), J3.10 (SHIELD), J5.MP (MountPin), R1.2, R2.2, R19.2, SW2.2, U1.3 (GND), U1.11 (GND), U1.15 (GND), U1.17 (PAD), U2.2 (GND), U3.5 (GND), U3.43 (GND), U3.44 (GND), U3.47 (GND), U3.50 (GND), U3.53 (GND), U3.78 (GND), U3.80 (GND), U3.87 (GND); also elsewhere on the board
unnamed: D1.2 (A), J1.1
unnamed: D3.2 (A), R3.2
unnamed: D4.2 (A), R11.2
unnamed: D5.2 (A), R16.2
unnamed: J5.1, U1.9 (OUTP)
unnamed: J5.2, U1.10 (OUTN)
unnamed: RN4.8 (R1.2), U3.81 (LCD_HSYNC)
unnamed: RN4.7 (R2.2), U3.82 (LCD_VSYNC)
unnamed: RN4.6 (R3.2), U3.83 (LCD_DE)
unnamed: RN4.5 (R4.2), U3.79 (LCD_CLK)
unnamed: R19.1, U1.2 (GAIN_SLOT)
unnamed: R18.2, U1.4 (~SD_MODE)
VBAT: BT2.P, U3.86 (VBAT)
VBUS: C1.1, C11.1, D1.1 (K), L1.1, U1.7 (VDD), U1.8 (VDD), U2.5 (VIN), U3.41 (VIN); also elsewhere on the board
VDD_LCD: C5.1, C6.1, FB1.2, J2.36

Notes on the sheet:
30mA

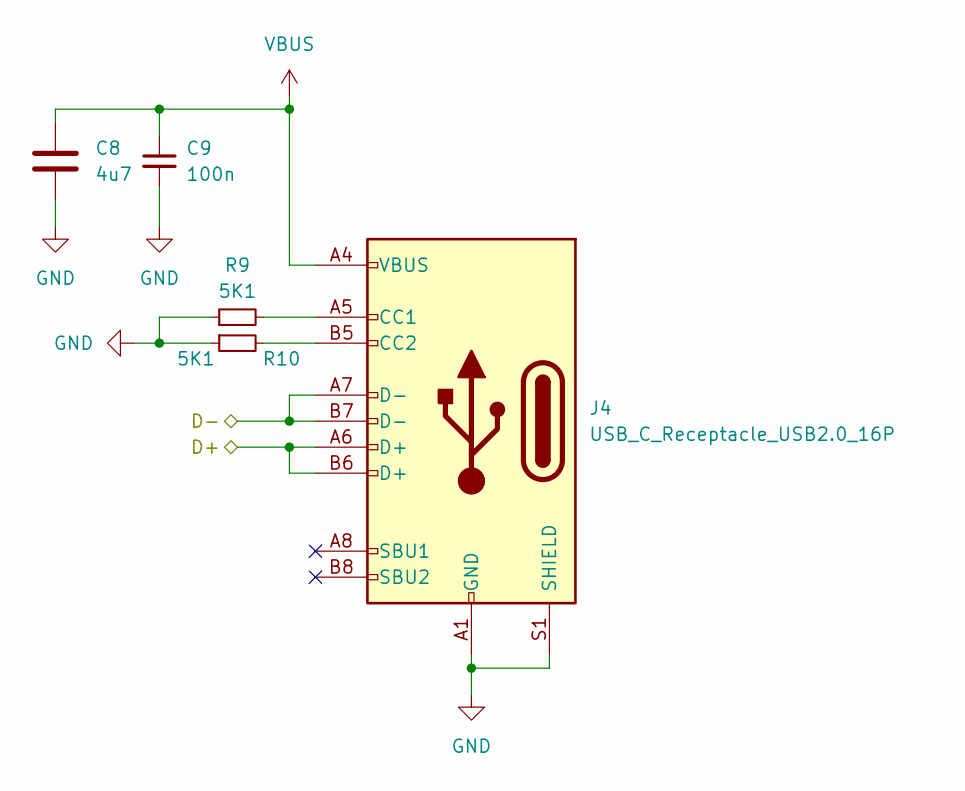
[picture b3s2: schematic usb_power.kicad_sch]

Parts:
C8: 4u7; C_0805_2012Metric; JLCPCB Part # C1779
C9: 100n; C_0402_1005Metric; JLCPCB Part # C307331
J4: USB_C_Receptacle_USB2.0_16P; USB_C_Receptacle_G-Switch_GT-USB-7010ASV; JLCPCB Part # C963412
R9, R10: 5K1; R_0402_1005Metric; JLCPCB Part # C25905

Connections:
/USB_DN: J4.A7 (D-), J4.B7 (D-); also elsewhere on the board
/USB_DP: J4.A6 (D+), J4.B6 (D+); also elsewhere on the board
GND: C8.2, C9.2, J4.A1 (GND), J4.A12 (GND), J4.B1 (GND), J4.B12 (GND), J4.S1 (SHIELD), R9.1, R10.1; also elsewhere on the board
unnamed: J4.A5 (CC1), R9.2
unnamed: J4.B5 (CC2), R10.2
VBUS: C8.1, C9.1, J4.A4 (VBUS), J4.A9 (VBUS), J4.B4 (VBUS), J4.B9 (VBUS); also elsewhere on the board

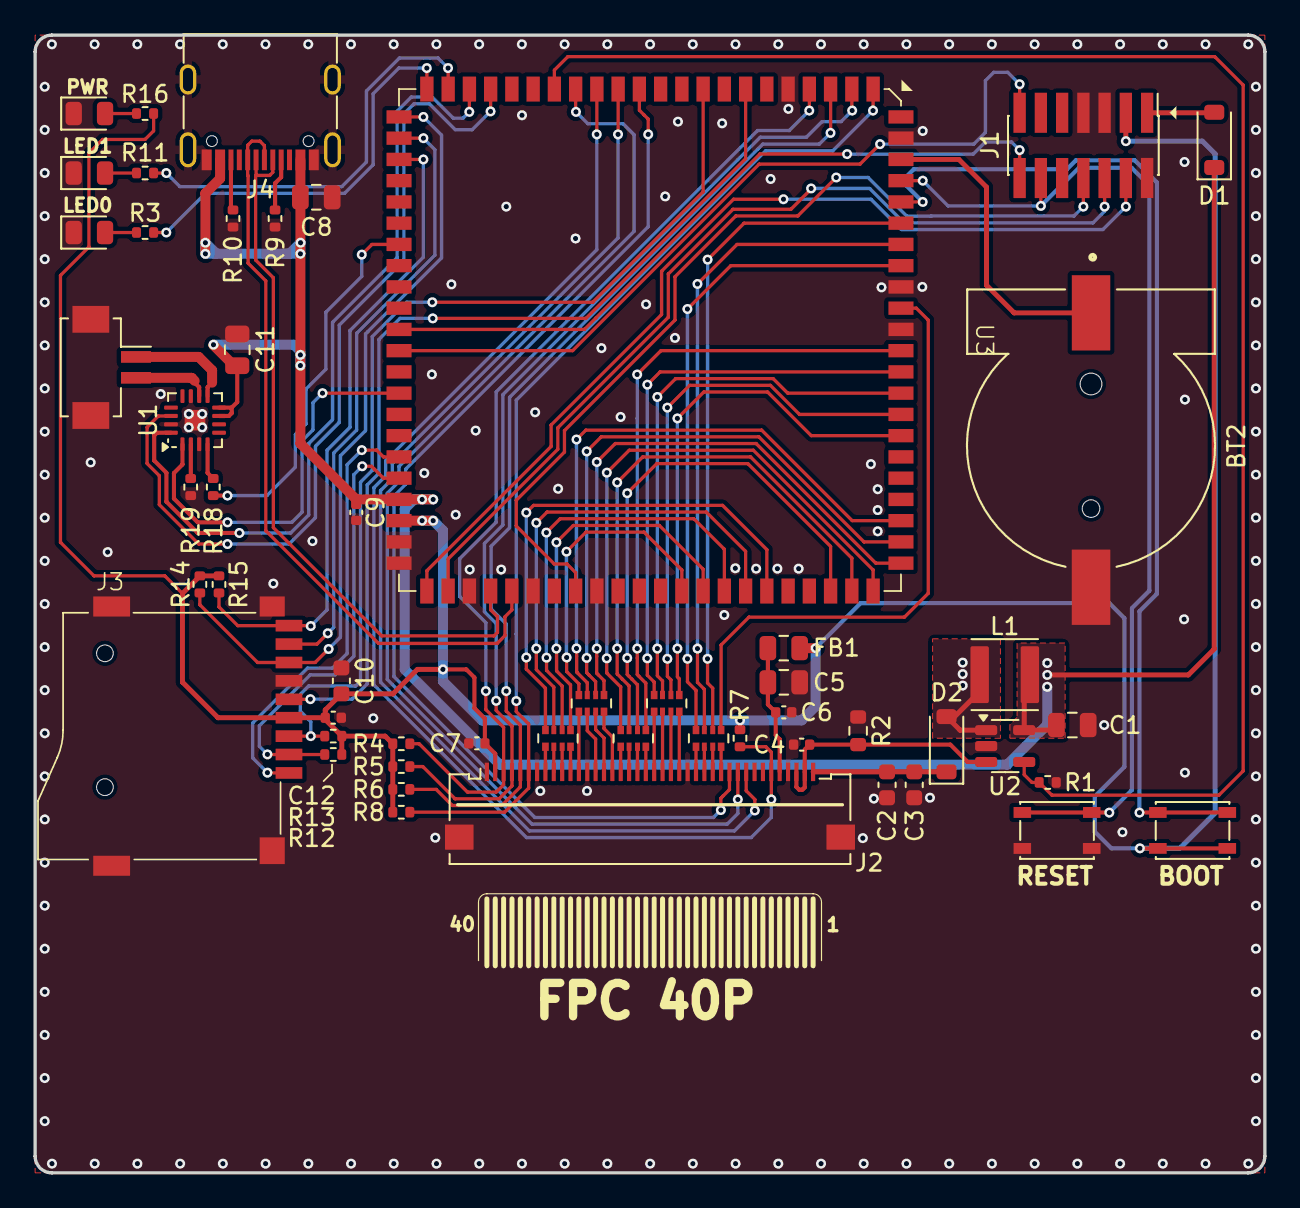
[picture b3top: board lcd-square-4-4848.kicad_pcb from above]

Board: 2 copper layers, 73.5 x 68.0 mm, 53 parts (0 on the bottom side), 89 nets.
